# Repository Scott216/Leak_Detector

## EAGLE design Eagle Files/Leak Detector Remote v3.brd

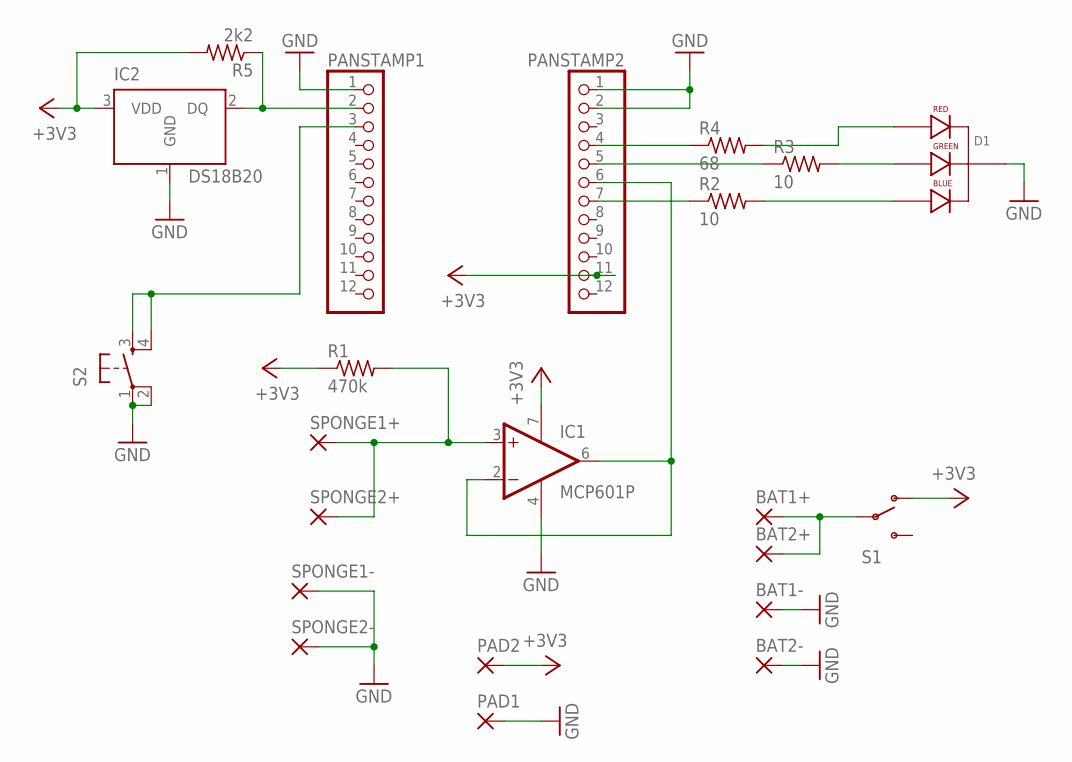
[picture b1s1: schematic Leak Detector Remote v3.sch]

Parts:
BAT1+, BAT1-, BAT2+, BAT2-: 3,81/1,4
D1: LED-RGB-CC-THRUCLEAR; LED-RGB-THRU
IC1: MCP601P; DIL08
IC2: DS18B20; TO-92
PAD1, PAD2: 1,6/0,9
PANSTAMP1, PANSTAMP2: PINHD-1X12; 1X12
R1: 470k; 0204/7
R2, R3: 10; 0204/7
R4: 68; 0204/7
R5: 2k2; 0204/7
S1: SWITCH-SPDTKIT; SWITCH-SPDT_KIT
S2: TAC_SWITCHPTH; TACTILE-PTH
SPONGE1+, SPONGE1-, SPONGE2+, SPONGE2-: 3,81/1,4

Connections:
+3V3: IC1.7 (V+), IC2.3 (VDD), PAD2.1, PANSTAMP2.11, R1.1, R5.2, S1.1 (O)
D3: PANSTAMP2.7, R2.1
D4: IC1.2 (-IN), IC1.6 (OUT), PANSTAMP2.6
D5: PANSTAMP2.5, R3.1
D6: PANSTAMP2.4, R4.1
D8: IC2.2 (DQ), PANSTAMP1.2, R5.1
D9: PANSTAMP1.3, S2.3, S2.4
GND: BAT1-.1, BAT2-.1, D1.2 (CATHODE), IC1.4 (V-), IC2.1 (GND), PAD1.1, PANSTAMP1.1, PANSTAMP2.1, PANSTAMP2.2, S2.1, S2.2, SPONGE1-.1, SPONGE2-.1
unnamed: IC1.3 (+IN), R1.2, SPONGE1+.1, SPONGE2+.1
unnamed: BAT1+.1, BAT2+.1, S1.2
unnamed: D1.1 (RED_CATHODE), R4.2
unnamed: D1.3 (GREEN_CATHODE), R3.2
unnamed: D1.4 (BLUE_CATHODE), R2.2

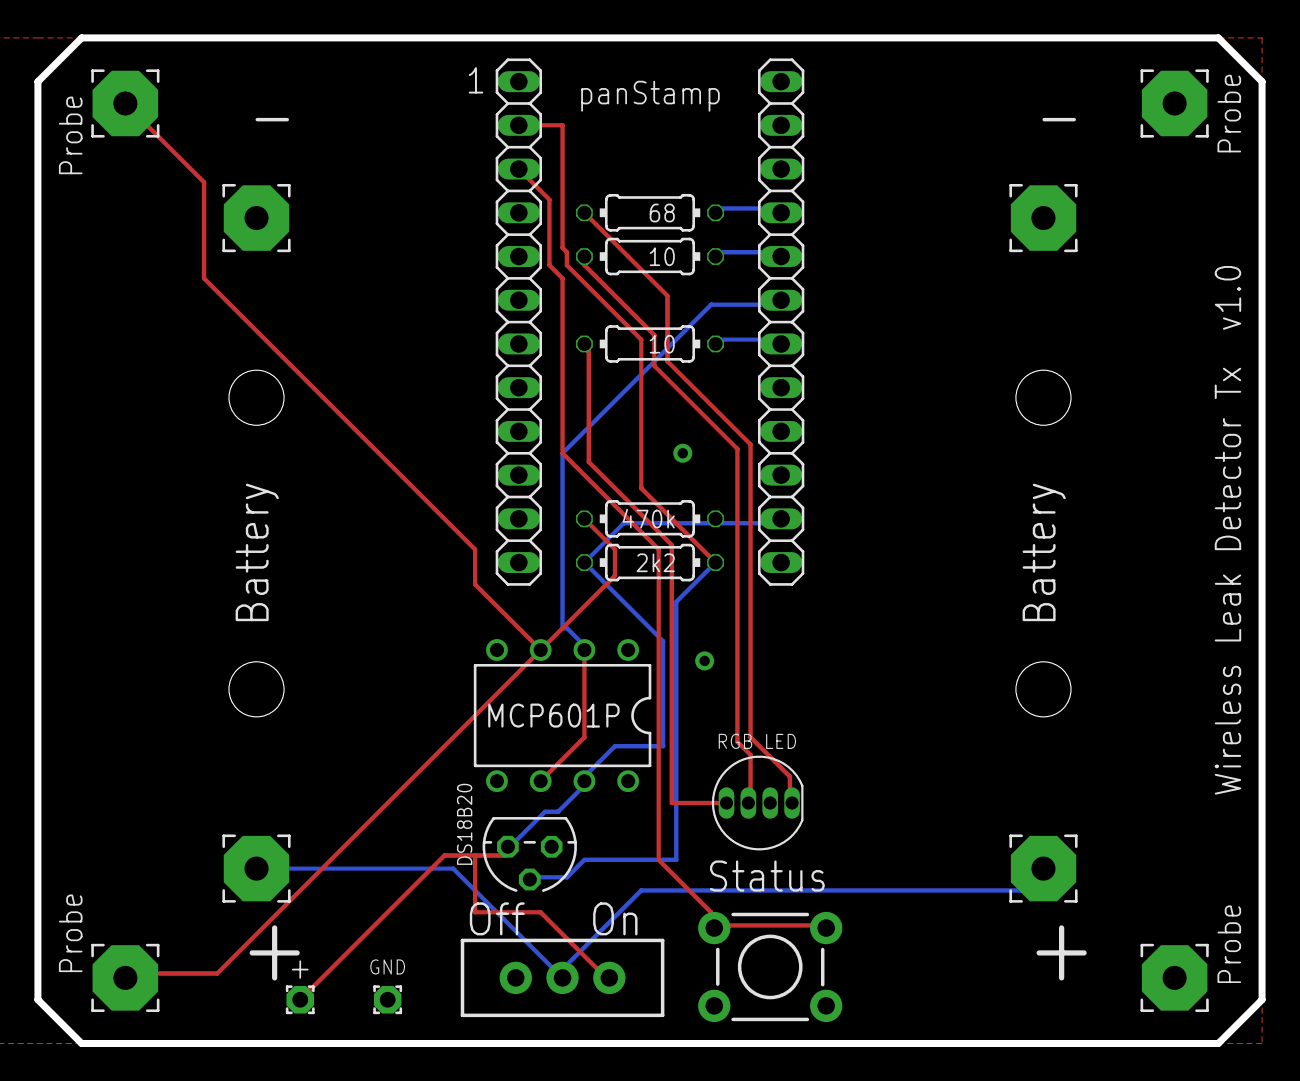
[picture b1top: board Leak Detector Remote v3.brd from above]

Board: 2 copper layers, 71.1 x 58.4 mm, 22 parts (0 on the bottom side), 13 nets.

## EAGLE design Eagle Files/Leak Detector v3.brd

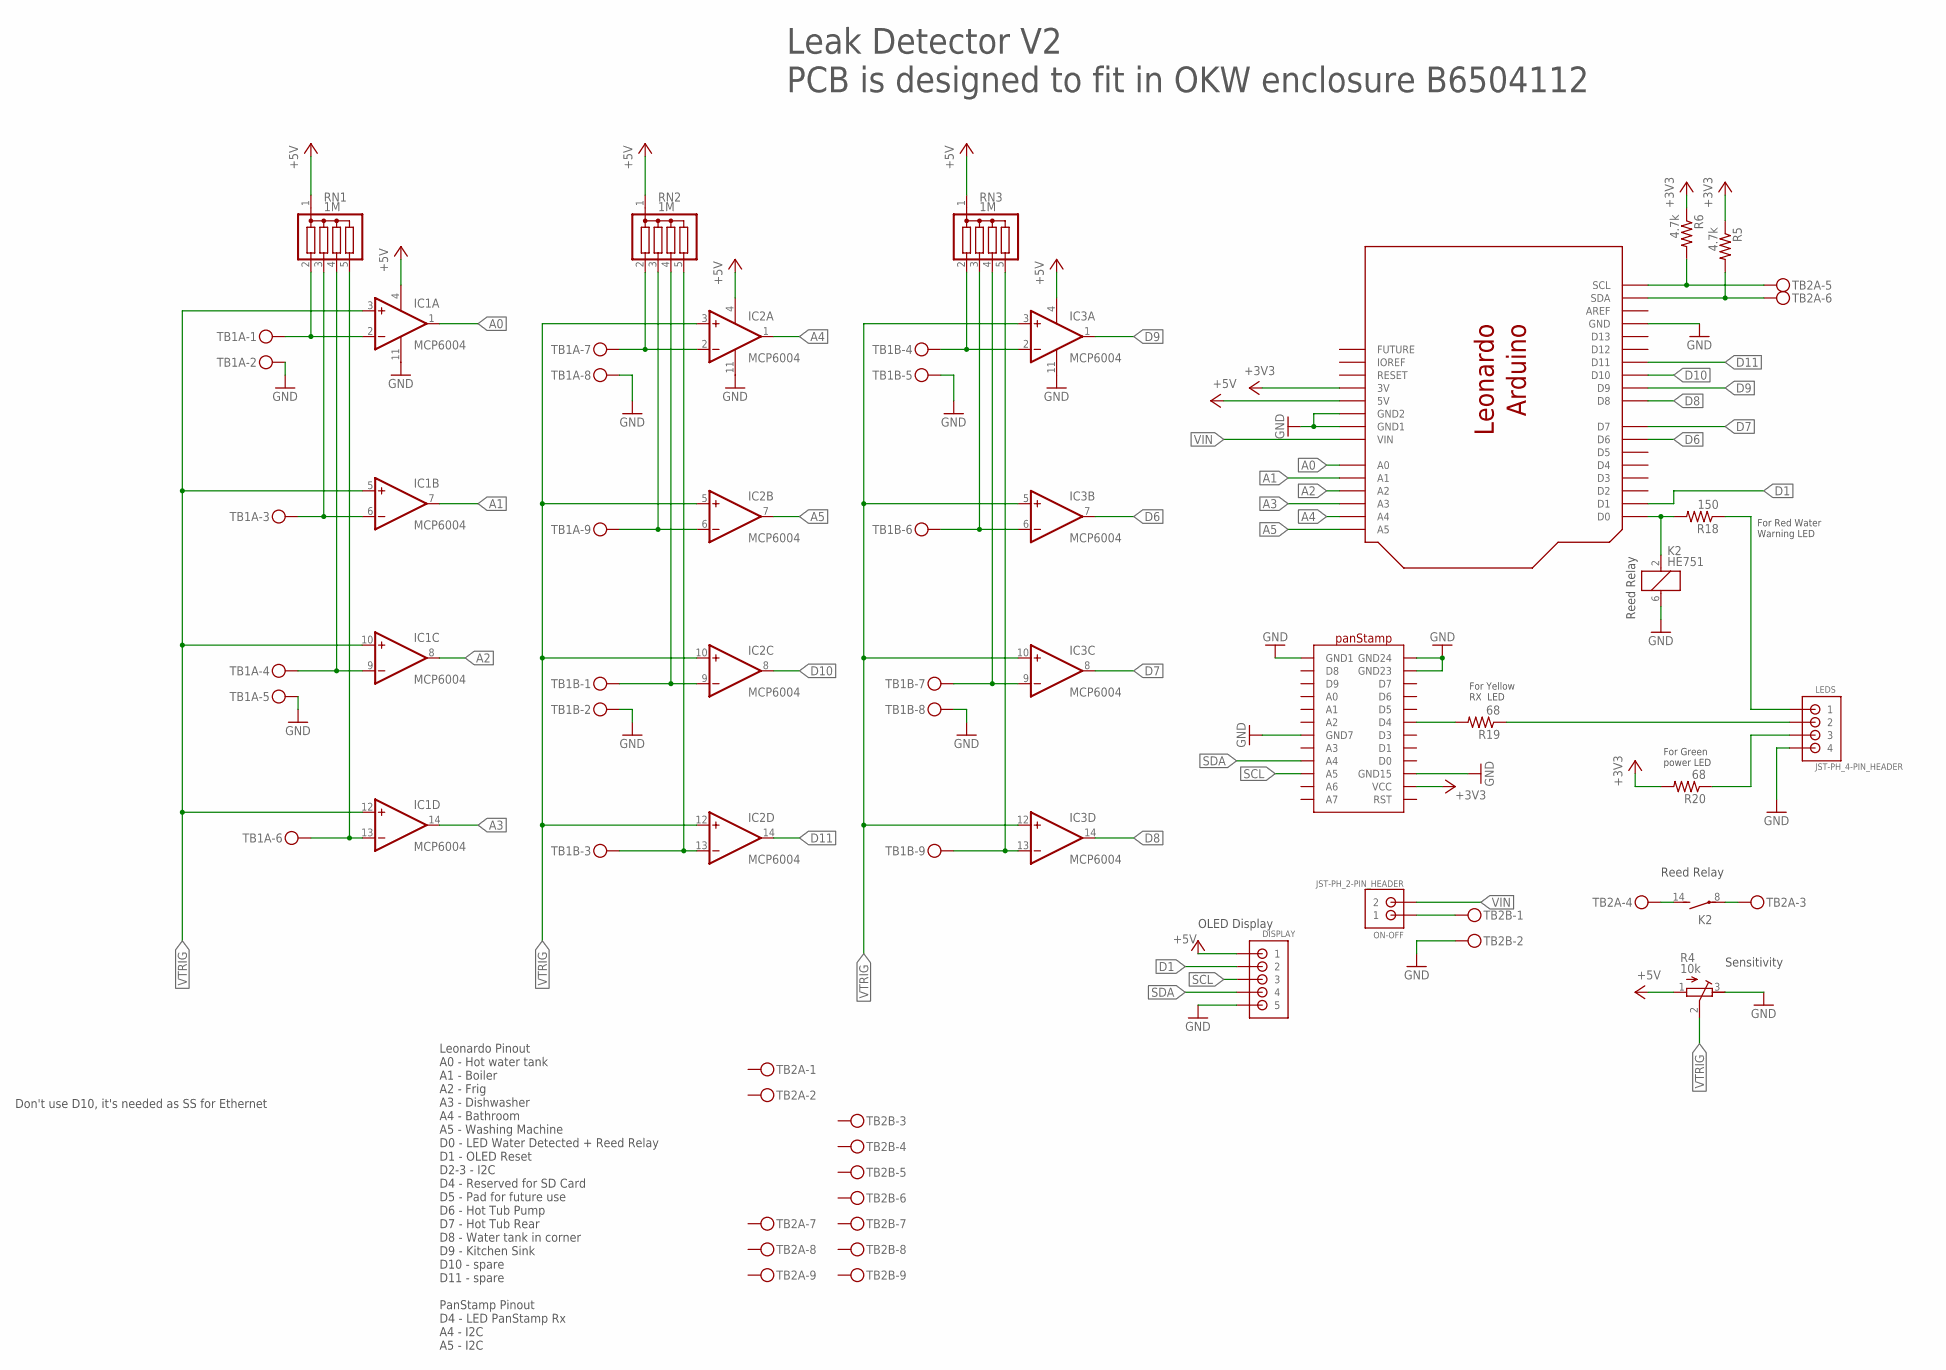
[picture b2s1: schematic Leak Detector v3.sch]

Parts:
DISPLAY: JST-PH_5-PIN_HEADER; JST_B5B-PH_HEADER
IC1, IC2, IC3: MCP6004; DIL14
K2: HE751
LEDS: JST-PH_4-PIN_HEADER; JST_B4B-PH_HEADER
ON-OFF: JST-PH_2-PIN_HEADER; JST_B2B-PH_HEADER
R4: 10k; RTRIM3296P
R5, R6: 4.7k; 0207/10
R18: 150; 0207/10
R19, R20: 68; 0207/10
RN1, RN2, RN3: 1M; SIL5
TB1A, TB1B, TB2A, TB2B: MKDSN1,5/9-5,08
U$1: ARDUINO_LEONARDO
U$2: PANSTAMP

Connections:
+3V3: R5.1, R6.1, R20.2, U$1.3V, U$2.VCC
+5V: DISPLAY.P1 (1), IC1.4 (V+), IC2.4 (V+), IC3.4 (V+), R4.1 (E), RN1.1, RN2.1, RN3.1, U$1.5V
A0: IC1.1 (OUT), U$1.A0
A1: IC1.7 (OUT), U$1.A1
A2: IC1.8 (OUT), U$1.A2
A3: IC1.14 (OUT), U$1.A3
A4: IC2.1 (OUT), U$1.A4
A5: IC2.7 (OUT), U$1.A5
BATHROOM: IC2.2 (-IN), RN2.2, TB1A.7
BOILER: IC1.6 (-IN), RN1.3, TB1A.3
D1: DISPLAY.P2 (2), U$1.D1
D6: IC3.7 (OUT), U$1.D6
D7: IC3.8 (OUT), U$1.D7
D8: IC3.14 (OUT), U$1.D8
D9: IC3.1 (OUT), U$1.D9
D10: IC2.8 (OUT), U$1.D10
D11: IC2.14 (OUT), U$1.D11
DISHWASHER: IC1.13 (-IN), RN1.5, TB1A.6
FRIG: IC1.9 (-IN), RN1.4, TB1A.4
GND: DISPLAY.P5 (5), IC1.11 (V-), IC2.11 (V-), IC3.11 (V-), K2.6 (2), LEDS.P4 (4), R4.3 (A), TB1A.2, TB1A.5, TB1A.8, TB1B.2, TB1B.5, TB1B.8, TB2B.2, U$1.GND, U$1.GND$2 (GND2), U$1.GND$3 (GND1), U$2.GND1, U$2.GND7, U$2.GND15, U$2.GND23, U$2.GND24
HAVEPOWER: LEDS.P3 (3), R20.1
HOT_TUB_PUMP: IC3.6 (-IN), RN3.3, TB1B.6
HOT_TUB_REAR: IC3.9 (-IN), RN3.4, TB1B.7
HOT_WATER_TANK: IC1.2 (-IN), RN1.2, TB1A.1
ISWATER: LEDS.P1 (1), R18.1
unnamed: ON-OFF.P1 (1), TB2B.1
unnamed: K2.2 (1), R18.2, U$1.D0
unnamed: K2.14 (S), TB2A.4
unnamed: K2.8, TB2A.3
unnamed: R19.2, U$2.D4
RXOK: LEDS.P2 (2), R19.1
SCL: DISPLAY.P3 (3), R6.2, TB2A.5, U$1.SCL, U$2.A5
SDA: DISPLAY.P4 (4), R5.2, TB2A.6, U$1.SDA, U$2.A4
SINK: IC3.2 (-IN), RN3.2, TB1B.4
SPARE1: IC2.9 (-IN), RN2.4, TB1B.1
SPARE2: IC2.13 (-IN), RN2.5, TB1B.3
VIN: ON-OFF.P2 (2), U$1.VIN
VTRIG: IC1.3 (+IN), IC1.5 (+IN), IC1.10 (+IN), IC1.12 (+IN), IC2.3 (+IN), IC2.5 (+IN), IC2.10 (+IN), IC2.12 (+IN), IC3.3 (+IN), IC3.5 (+IN), IC3.10 (+IN), IC3.12 (+IN), R4.2 (S)
WASH_MACH: IC2.6 (-IN), RN2.3, TB1A.9
WATER_TANK: IC3.13 (-IN), RN3.5, TB1B.9

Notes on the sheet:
Leonardo Pinout A0 - Hot water tank A1 - Boiler A2 - Frig A3 - Dishwasher A4 - Bathroom A5 - Washing Machine D0 - LED Water Detected + Reed Relay D1 - OLED Reset D2-3 - I2C D4 - Reserved for SD Card D5 - Pad for future use D6 - Hot Tub Pump D7 - Hot Tub Rear D8 - Water tank in corner D9 - Kitchen S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
Leak Detector V2 PCB is designed to fit in OKW enclosure B6504112
OLED Display
Reed Relay
Sensitivity
For Green power LED
For Yellow RX LED
For Red Water Warning LED
Don't use D10, it's needed as SS for Ethernet

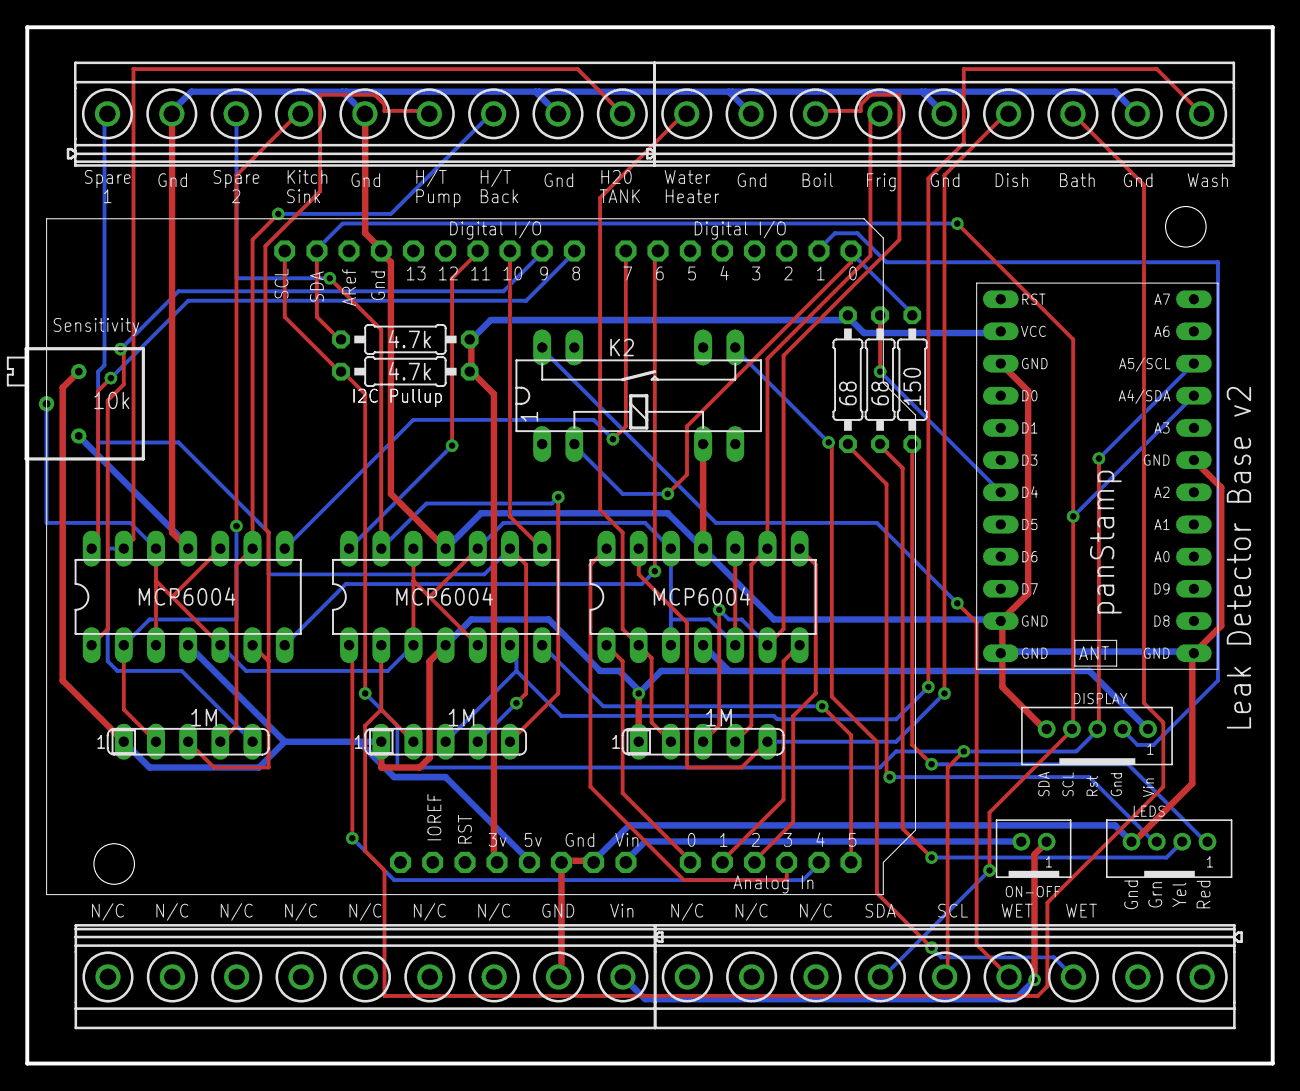
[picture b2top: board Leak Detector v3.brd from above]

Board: 2 copper layers, 98.3 x 81.8 mm, 22 parts (0 on the bottom side), 40 nets.

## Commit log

2020-11-06 New ver 1.00 using RPi & python
2020-11-08 added e-ink code
2020-11-10 added e-ink display
2020-11-13 v1.02 - ready run
2021-01-08 v1.03 - added buzzer output
2021-02-18 ver 1.04 minor fixes
2021-02-19 ver 1.05 printout changes
2022-10-15 v1.08
2022-10-18 Arduino (Panstamp) Wireless Receiver
2022-10-18 Arduino (Panstamp) Wireless Transmitter
2022-10-18 Schematic and board file for wireless transmitter
2023-03-02 v1.10 Public IP
    Added public IP to weekly Sunday status text message
2023-03-14 v1.11 Bug - missing statusMsg
    Fixed bug introduced in v1.10

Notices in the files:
parts and their libraries:
SparkFun-Electromechanical: Licensing: CC v3.0 Share-Alike You are welcome to use this library for commercial purposes.
